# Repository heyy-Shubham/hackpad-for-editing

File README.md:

h## Hackpad For Editing

## Why I Built This

As a video editor, I was tired of reaching across the keyboard
for shortcuts like Undo, Redo, and Zoom constantly.
I wanted a dedicated device that keeps my hands in the editing
zone — so I built the Hackpad For Editing.

I will make this device using 9 sw_cherry_mx (switch) and encoder and 0.91 oled display
just plug and enhance editing leval build for editors

## What does this do
9 sw_cherry_mx mechanichl switch , Every switch maped editing shortcut 
rotary encoder for layer moveing left And right
Using Like a Standerd Usb Keyboard
Firamware using PlatformIO + keyboard.h in raspbarry pi pico micro controllar

## keyboard shortcuts
| key | Shortcut | Funcation |
|------|-----------|-----------|
| SW1 | Tab | Switch between panel |
| SW2 | Win + Swift + S | Screemshot |
| SW3 | Ctrl z | undo |
| SW4 | Ctrl + Swift + z | Redo |
| SW5 | End | Jumpto the end time line |
| SW6 | Alt + 2 | Application specific Shortcut |
| SW7 | Ctrl + B | Split Clip |
| SW8 | Ctrl + = | Zoom in |
| SW9 | Ctrl + - | Zoom Out |
| Encoder Clockwise | Rise Arrow | Time line forward |
| Encoder Anti-Clockwise | Left Arrow | Backward |

## Connectioms Of Respberry To switches
| Component | Pin | 
|-----------|------|
| SW1 | D2 |
| SW2 | D3 |
| SW3 | D4 |
| SW4 | D5 |
| SW5 | D6 |
| SW6 | D7 |
| SW7 | D8 |
| SW8 | D9 |
| SW9 | D10 |
| Encoder  A | D20 |
| Encoder  B | D21 |

# Component 
1. Switch (sw_cherry_mx)
2. Custom Design PCB
3. Encoder
4. 0.91inch OLED Display
5. Enclosure 

## Firamware Flash in Respberry pi pico
 1. install vs code (https://code.visualstudio.com/)
 2. Add Extension PlatformIO Extension
 3. Select Board And install Firamware

# Fallout Zine Page

## PCB

# Cad Source File 
OneShap Project Link:
https://cad.onshape.com/documents/5b5dae307a075cbb770b9d40/w/47bce3600617231dbb59e220/e/9a00e2926e7c151da0a35bf5

## CAD

##Author
Shubham Raj - @heyy-Shubham(https://github.com/heyy-shubham)

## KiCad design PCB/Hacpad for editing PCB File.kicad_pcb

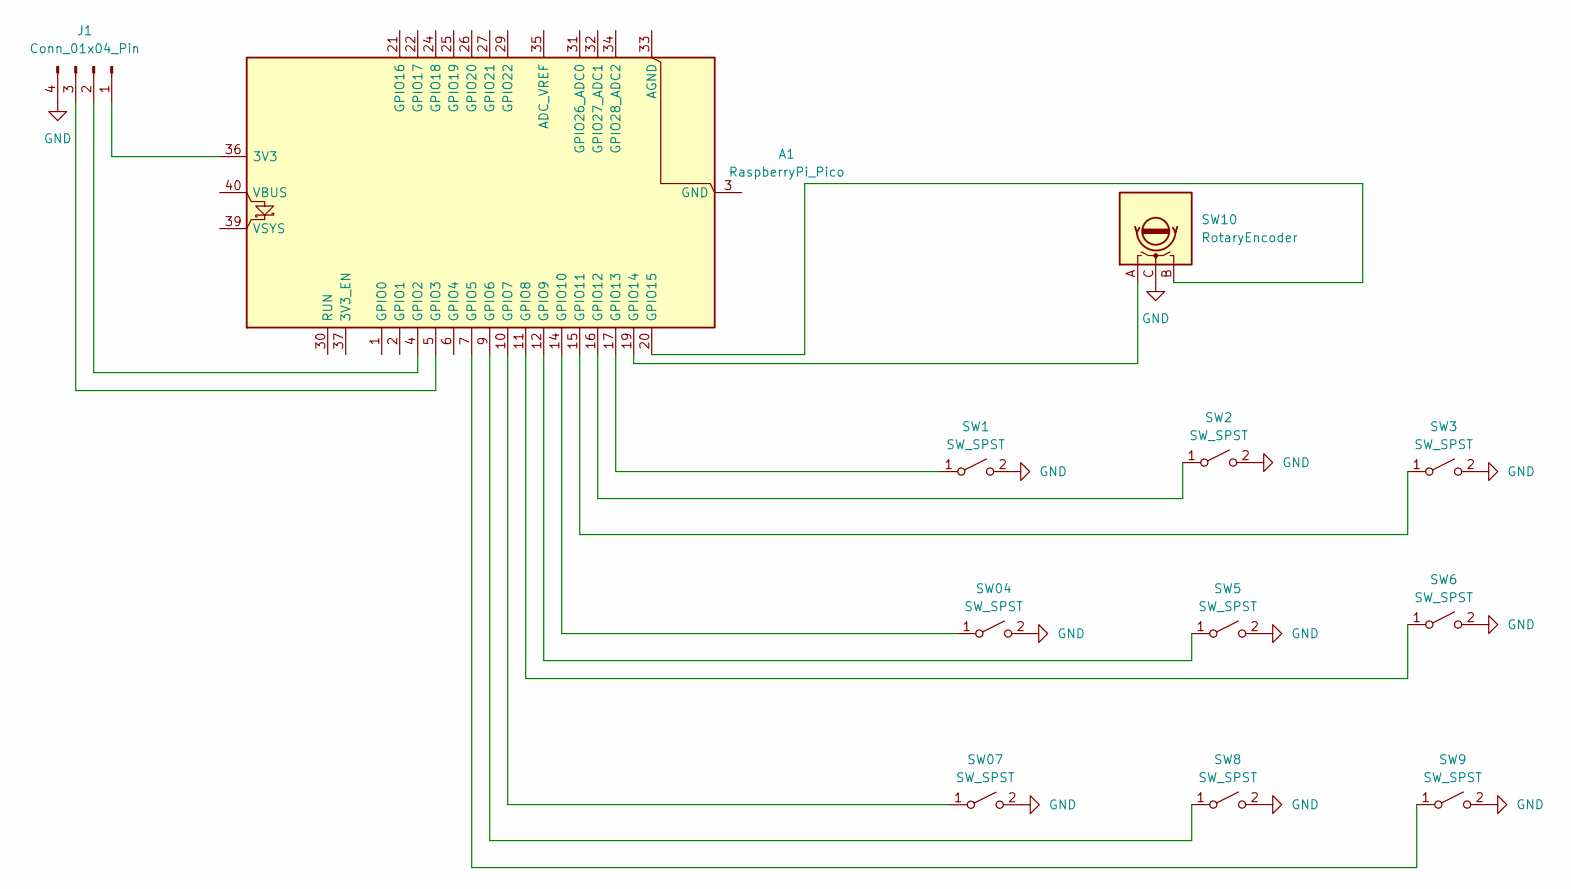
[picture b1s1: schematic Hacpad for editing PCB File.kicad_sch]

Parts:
A1: RaspberryPi_Pico; RaspberryPi_Pico_Common_Unspecified
J1: Conn_01x04_Pin; PinHeader_1x04_P2.54mm_Vertical
SW1, SW2, SW3, SW04, SW5, SW6, SW07, SW8, SW9: SW_SPST; SW_Cherry_MX_1.00u_PCB
SW10: RotaryEncoder; RotaryEncoder_Alps_EC11E-Switch_Vertical_H20mm

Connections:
GND: J1.4, SW1.2 (B), SW2.2 (B), SW3.2 (B), SW04.2 (B), SW5.2 (B), SW6.2 (B), SW07.2 (B_2), SW8.2 (B), SW9.2 (B), SW10.C
unnamed: A1.36 (3V3), J1.1
unnamed: A1.3 (GND), A1.8 (GND), A1.13 (GND), A1.18 (GND), A1.23 (GND), A1.28 (GND), A1.38 (GND)
unnamed: A1.4 (GPIO2), J1.2
unnamed: A1.5 (GPIO3), J1.3
unnamed: A1.7 (GPIO5), SW9.1 (A)
unnamed: A1.9 (GPIO6), SW8.1 (A)
unnamed: A1.11 (GPIO8), SW6.1 (A)
unnamed: A1.12 (GPIO9), SW5.1 (A)
unnamed: A1.14 (GPIO10), SW04.1 (A)
unnamed: A1.15 (GPIO11), SW3.1 (A)
unnamed: A1.16 (GPIO12), SW2.1 (A)
unnamed: A1.17 (GPIO13), SW1.1 (A)
unnamed: A1.19 (GPIO14), SW10.A
unnamed: A1.20 (GPIO15), SW10.B

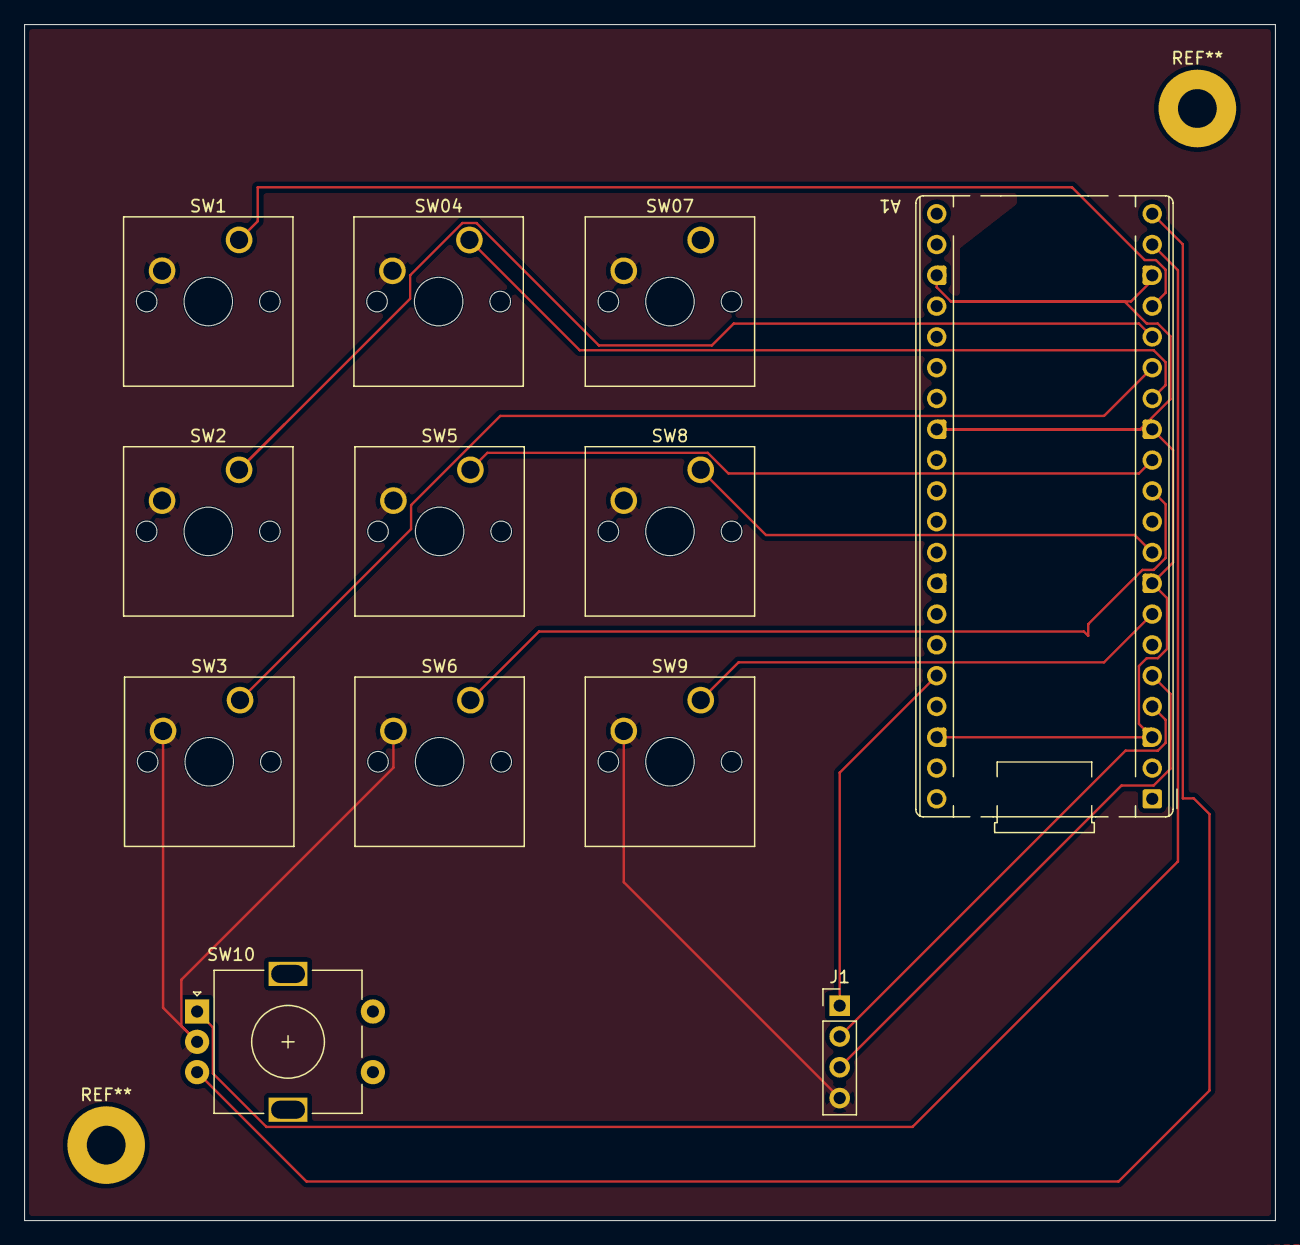
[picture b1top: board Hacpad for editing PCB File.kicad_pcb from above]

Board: 2 copper layers, 103.2 x 98.6 mm, 12 parts (0 on the bottom side), 15 nets.

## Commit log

2026-04-23 Add Arduino keyboard control for multiple buttons code
    A PlatformIO-based project for efficient code editing and embedded development using VS Code.
2026-04-23 CAD
    This is a encloser cad model for hackpad editor
2026-04-23 schematic of pcb
2026-04-26 Revise README for clarity and correct typos
    Updated project description, tech stack, features, and author information in README.md.
2026-04-26 Fix typos and enhance formatting in README.md
    Corrected typos and improved formatting in the README.
2026-04-26 schematic
    schematic for PCB
2026-04-26 Enhance README with usage steps and project rationale
    Added usage instructions and project motivation to README.
2026-04-27 Fix placeholder formatting in placeholder.md
2026-04-27 Add placeholder.md file
2026-04-27 Add placeholder markdown file
2026-04-27 Rename main.cpp to Firmware/main.cpp
2026-04-27 Rename Part Studio 2 - Part 5 (1).stl to CAD/Part Studio 2 - Part 5 (1).stl
2026-04-27 Rename Part Studio 2 - Part 6.stl to CAD/Part Studio 2 - Part 6.stl
2026-04-27 Rename made by Shubham.kicad_sch to PCB/made by Shubham.kicad_sch
2026-04-27 Delete/placeholder.md
2026-04-27 Remove placeholder text from placeholder.md
2026-04-27 PCB of Hackpad for editing
2026-04-27 Rename placeholder.md to placeholder
2026-04-27 Cad of our encloser
2026-04-27 Top Case of Encloser
2026-04-27 PCB Image
2026-04-27 Rename main.cpp to main.cpp
2026-04-27 Rename 20260427_140940.jpg to 20260427_140940.jpg
2026-04-27 Rename Screenshot 2026-04-27 134819.png to Screenshot 2026-04-27 134819.png
2026-04-27 Rename Screenshot 2026-04-27 134920.png to Screenshot 2026-04-27 134920.png
2026-04-27 Rename {22AD9E3E-82CF-440B-9E48-9809F0ACCEAE}.png to {22AD9E3E-82CF-440B-9E48-9809F0ACCEAE}.png
2026-04-27 Rename Assets/{4853B936-79CA-4EE4-9DD8-A8C7A89B42EC}.png to Assets{4853B936-79CA-4EE4-9DD8-A8C7A89B42EC}.png
2026-04-27 Fix image paths in README.md
    Updated image paths in README.md to correct asset references.
2026-04-27 Fix image filename in README.md
2026-04-27 Rename Screenshot 2026-04-27 134819.png to Screenshot2026-04-27134819.png
2026-04-27 Rename Screenshot 2026-04-27 134920.png to pcb.jpg
2026-04-27 Rename pcb.jpg to pcb.jpg
2026-04-27 Rename Screenshot2026-04-27134819.png to haclpad_pcb_jpg
2026-04-27 Rename Assets{4853B936-79CA-4EE4-9DD8-A8C7A89B42EC}.png to Assets/{4853B936-79CA-4EE4-9DD8-A8C7A89B42EC}.png
2026-04-27 Enhance Readmi
2026-04-27 Rename haclpad_pcb_jpg to haclpad_pcb_png
2026-04-27 pcb.jpg
2026-04-27 Rename Screenshot 2026-04-27 134819.png to Hackpad.png
2026-04-27 Poster
2026-04-27 Fix image syntax and add poster section in README
    Updated image syntax for Hackpad and added a poster section.
2026-04-28 Rename section from 'Poster' to 'Fallout Zine Page'
2026-04-28 Magzine Page
2026-04-28 Rename Brown White Vintage Classic Minimalist Memo A5 Document_20260428_095524_0000.png to Magzine_page.png
2026-04-28 Rename Brown White Vintage Classic Minimalist Memo A5 Document_20260428_100751_0000.pdf to Fallout_magzine_page.pdf
2026-04-28 schematics of pcb
2026-04-28 Create LICENSE
2026-04-28 Rename Part Studio 2 - Part 5 (1).stl to Body.stl
2026-04-28 Rename Part Studio 2 - Part 6.stl to Top.stl
2026-05-10 Add OneShap project link to README
    Added OneShap project link for CAD source file.
2026-05-10 .step
2026-05-10 Encoloser Bottem STEP File
2026-05-10 Encloser Top STEP file
2026-05-10 Rename Hackpad_for_editing.pdf to Hackpad_for_editing_magzine.pdf
2026-05-10 Magzine Page Png
2026-05-10 Fix heading format and update image in README
    Updated headings and image reference in README.
